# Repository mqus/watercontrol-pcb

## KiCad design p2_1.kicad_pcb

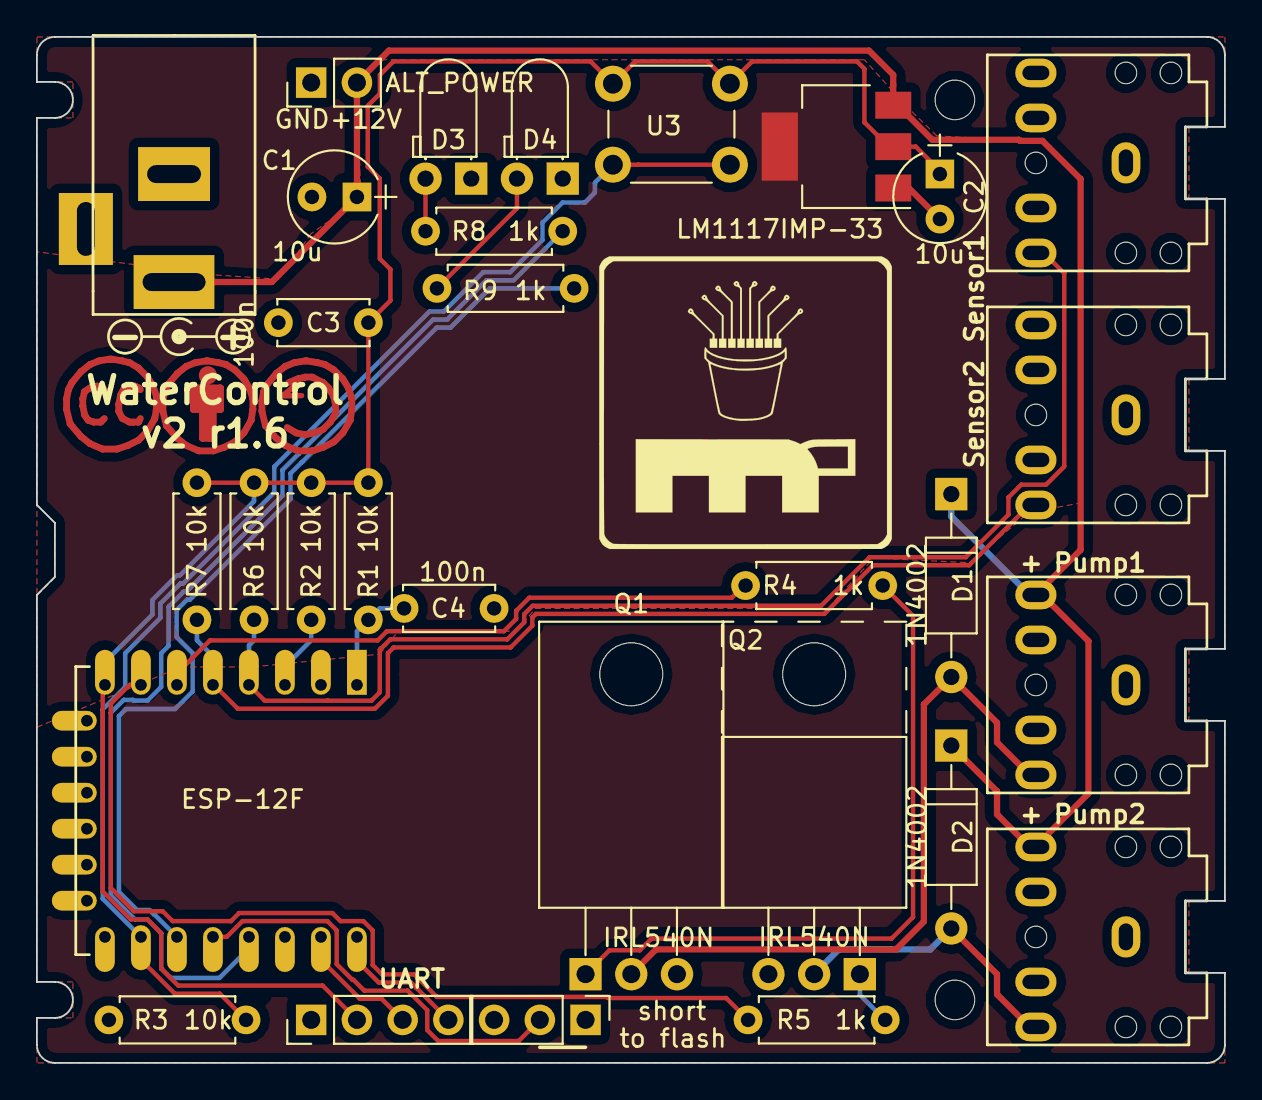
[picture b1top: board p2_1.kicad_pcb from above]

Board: 2 copper layers, 66.0 x 57.0 mm, 30 parts (0 on the bottom side), 21 nets.

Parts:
C1, C2: 10u; CP_Radial_Tantal_D5.0mm_P2.50mm
C3, C4: 100n; C_Disc_D5.0mm_W2.5mm_P5.00mm
D1, D2: 1N4002; D_A-405_P10.16mm_Horizontal
D3, D4: LED; LED_D3.0mm_Horizontal_O1.27mm_Z2.0mm
J1: BARREL_JACK; Barrel_Jack_5.5_2.1mm
J2: FLASH_JMP; Pin_Header_Straight_1x03_Pitch2.54mm
J3: UART; Pin_Header_Straight_1x04_Pitch2.54mm
J4: ALT_POWER; Pin_Header_Straight_1x02_Pitch2.54mm
J5, J6, J7, J8: jack-3.5mm-5pin; 3.5mm_5pin_jack
Q1: IRL540N; TO-220_Horizontal
Q2: IRL540N; TO-220_Horizontal_Reversed
R1, R2, R3, R6, R7: 10k; R_Axial_DIN0207_L6.3mm_D2.5mm_P7.62mm_Horizontal
R4, R5, R8, R9: 1k; R_Axial_DIN0207_L6.3mm_D2.5mm_P7.62mm_Horizontal
U1: LM1117IMP-33; SOT-223
U2: ESP-12F; ESP-12E
U3: Switch; SW_PUSH_6mm

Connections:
+3V3: C2.1, C3.2, J3.2, R1.2, R2.2, R6.2, R7.1, U1.2, U2.8, U3.2
/12V: C1.1, D1.1, D2.1, J1.1, J4.2, J7.2, J8.2, U1.3
/GPIO0: J2.2, U2.12
/RXD0: J3.3, U2.15
/TXD0: J3.4, U2.16
/ctl1: J5.3, R6.1, U2.4
/ctl2: J6.3, R7.2, U2.5
/ctl3: R4.2, U2.6
/ctl4: R5.2, U2.7
/led1: R9.1, U2.11
/led2: R8.1, U2.13
GNDREF: C1.2, C2.2, C3.1, C4.1, D3.1, D4.1, J1.2, J2.1, J3.1, J4.1, J5.2, J6.2, Q1.3, Q2.3, R3.1, U1.1, U2.9
unnamed: C4.2, R1.1, U2.1
unnamed: D1.2, J7.3, Q1.2
unnamed: D2.2, J8.3, Q2.2
unnamed: D3.2, R8.2
unnamed: D4.2, R9.2
unnamed: Q1.1, R4.1
unnamed: Q2.1, R5.1
unnamed: R2.1, U2.3
unnamed: R3.2, U2.10, U3.1

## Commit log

2018-04-19 add documents
2019-08-26 Backup old state
